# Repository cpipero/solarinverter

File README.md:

# solarinverter
Kicad Project to build a programmable Solar Inverter

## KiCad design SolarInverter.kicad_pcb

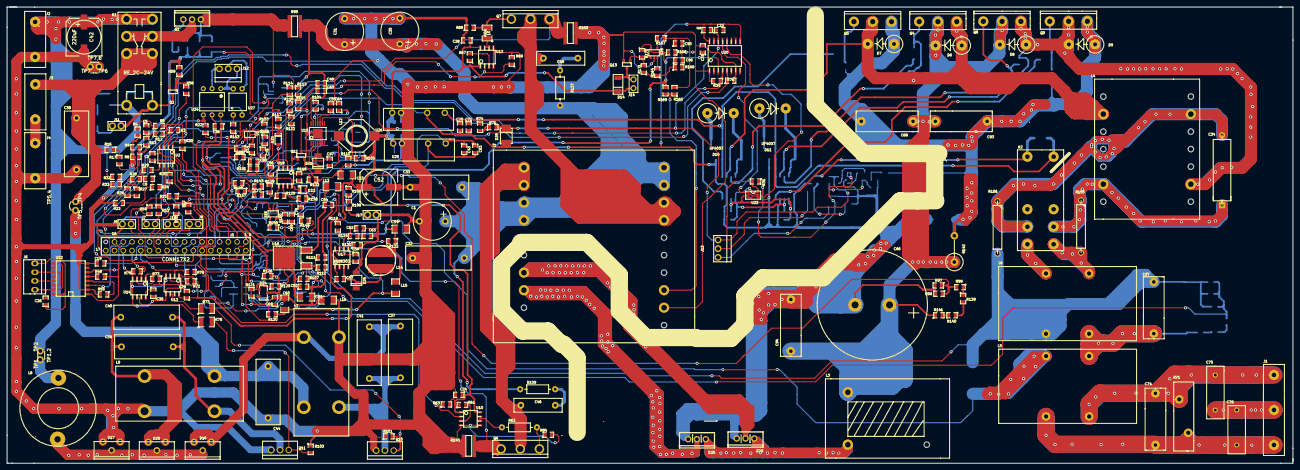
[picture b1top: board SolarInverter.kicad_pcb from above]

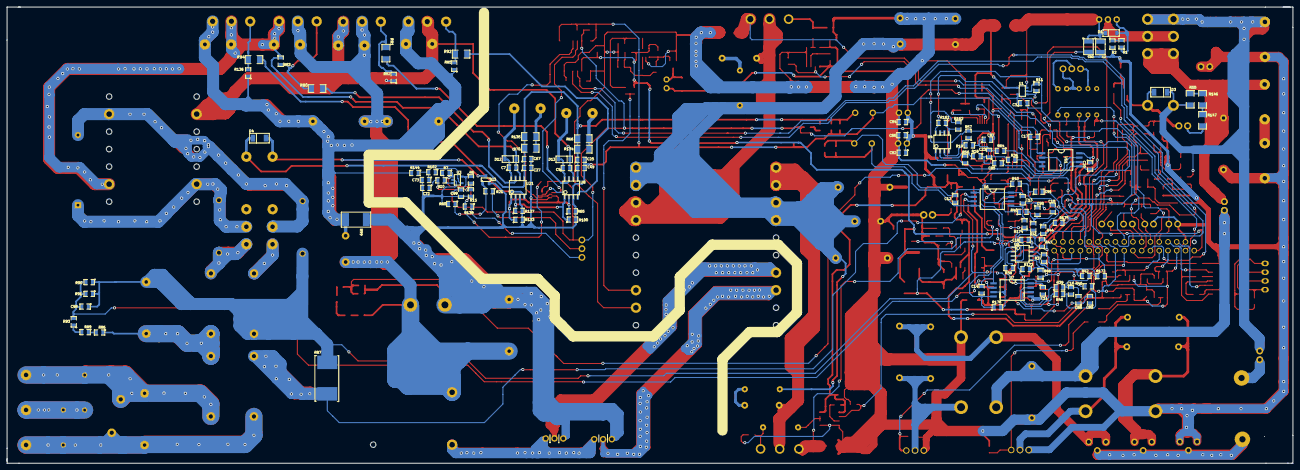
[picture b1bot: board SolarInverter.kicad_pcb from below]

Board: 2 copper layers, 373.0 x 132.3 mm, 370 parts (110 on the bottom side), 207 nets.

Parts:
C1, C31, C35: 2200uF; Elco18x37
C2, C92: 3.3uF; SM1210
C3, C6, C56, C65, C85, C87, C88, C89, C90, C91: 0.22uF; SM0805
C5, C8, C16, C23: 1nF; SM0805
C7, C9, C10, C64: 0.47uF; SM0805
C11, C12, C13, C14, C17, C20, C21, C22, C24, C25, C27, C28, C29, C30, C43, C48, C49, C54, C61, C67, C70, C71, C82, C83, C84, C86: 2.2uF; SM0805
C15: 2.2nF; SM0805
C18, C36, C72, C77, C80, C95, C96: 0.1uF; SM0805
C19, C26, C50, C69, C81, C99: 1uF; SM0805
C32, C33, C37, C38, C39, C40, C41, C44: 4.7uF; MetFilCap1807
C34: 1uF; CP8
C42: 220uF; SMDSVP10
C45, C46: 4700uF; MetFilCap13x4
C47, C57: 0.022uF; SM0805
C51, C53: 10uF; SM1206
C52: 470uF; SMDSVP10
C55: 4700pF; SM0805
C58: 10uF; SM0805
C59, C60: 22uF; SM1206
C62, C63, C73: 1000pF; SM0805
C66: 330uF; SnapCap30x40
C68, C74, C93, C94, C97: 0.15uF; MetFilCap2008
C75, C76: 2200pF; CP4
C78, C79: 47pF; SM0805
C98: 0.01uF; SM0805
D1: MMSZ5245B; SOD123
D3, D4, D14: RLS4148; SOD80
D6, D7, D8, D9, D10, D11: UF4007
D12, D13: MMSZ5245B-15V; SOD123
D16, D17, D20: MBR1560
D21, D25: STPS340; STPS340U
D22: BZM55C27
D23: MMSZ8V2T1G
D24: LM4041
D26, D29: PF60SA60DS
D28: 1SMB5918B
J1: CTB9550/3AO; Conn10mmX3
J2, J3, J4: BAT; Conn10mm
J5: CONN17X2; PinArray17x2
J6: HDR1X4WL; Molex22232041
J7, J8, J9, J10, J11, J17: JUMPERSEL; 2PinHeaer
J12, J13: CONN3PIN; Molex2031
J14: HDR1X2; HDR1x2
K1: RE_2C-24V; RE_2C_24V
K2: HRM1-S-12V; DPDTRelay
L3: 150uH; DMT21493L8
L4: 2X3.3mH; CoilL4
L5, L6: 2X6.8mH; PowerInductor1
L7, L9: 2X300uH; CMT1-.3-15L
L8: 47uH; PCV047310L
L12: 150uH; DO3316P-154KL
L13, L15, L16: 600OHM; SM1206
L14: 10uH; CDRH6D38NP
Q1: FQP47P06; FQP47P06TO220
Q2, Q3, Q12, Q13: BSS138LT1G; SOT23
Q4, Q5, Q8, Q9: FQA19N60; TO3PN
Q6, Q7: FDH3632
Q10, Q11: FDP3651U
R1, R2, R61, R67, R72, R77, R118, R124, R148, R152, R166: 22k; SM0805
R3, R5, R12, R20, R21, R24, R29, R53, R54, R59, R60, R117, R119, R132, R164, R165, R167, R168: 10k; SM0805
R4, R13, R23, R28, R51, R52, R163: 220; SM0805
R6: 20k; SM0805
R7: 1.5M; SM0805
R8, R26: 82k; SM0805
R9, R14, R15, R27, R120, R143, R149, R151, R153, R157, R158, R159: 1k; SM0805
R10, R84, R88, R101, R102, R103: 2.2k; SM0805
R11, R56, R57, R172, R173, R174, R175: 46.4k; SM0805
R16, R32: 27k; SM0805
R17, R33: 820; SM0805
R18, R19, R37, R38, R41, R42, R44, R46, R47, R48: 23.2k; SM0805
R22, R31, R34, R63, R65, R69, R75, R76, R79, R100, R127, R133, R150, R170: 4.7k; SM0805
R25, R30: 6.81k; SM0805
R36, R39, R40, R43, R45, R64: 3.32k; SM0805
R49, R58: 3.3k; SM0805
R50, R106, R108: 470; SM0805
R55, R146, R147: 1.5k; SM1206
R62, R109, R137: 10; CF14CT52R100J
R66, R70, R134, R135: 5.6; SM1206
R68, R73, R78: 10; SM1210
R71, R74, R138: 390; SM0805
R80, R81, R92, R94: 10; SM1206
R82, R83, R85, R96, R111, R112, R129, R136: 1.5k; SM0805
R86, R89, R93, R98, R139, R140, R141: 750k; SM0805
R87: 0.1; MetalStripR
R90, R144: 1.2k; SM0805
R91, R97: 1M; SM0805
R95, R145, R160: R005; FCSL64R005FER
R99: 0.05; RES2512
R104, R113, R115, R116, R126, R128, R130, R161, R162: 47k; SM0805
R105: 6.8k; SM0805
R107: 240; SM0805
R110, R125: 1.8k; SM0805
R114: 3.3.k; SM0805
R121: 5.1k; SM0805
R122, R171: 10M; SM0805
R123: 120k; SM0805
R131: 2.21k; SM0805
R142: 1.8M; R1WVERT
R155, R156: 330; R6
R169: 43k; SM0805
R176: 0; SM0805
RV1: 20S0271; VARISTOR
T1: ETD49
TP1,2: TP1___TP2; TP2PIN
TP5,4: TP5___TP4; TP2PIN
TP7,6: TP7___TP6; TP2PIN
U1: INA169
U2, U4, U9: AD8552; so-8
U3, U5, U19, U28: LMV7235M5; INA169
U6, U7, U11: ACPL-C78A; ACPL-C78A-060E
U8, U21: FAN7390; so-8
U10, U12, U13, U14: FAN3122; so-8
U15: LM5010A
U16: LM317MDT; DPAK2
U17: FAN8303; so-8
U18: LM393; so-8
U20: ADUM2200
U22: ADM2484E; SOIC16-W
U23: NL27WZ08
U24: PC900V0NSZXF
U25: MEV1S1205SC
U26: NMK1215SAC; MEV1S1205SC
U27: PS2561

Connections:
+1.65V_REF: C61.1, D24.2, R25.1, R30.1, R47.2, R48.1, R120.2, R121.1
+3.3V: C19.1, C21.1, C59.1, C69.1, C81.1, J5.A7, J5.B6, L14.2, L15.1, R22.1, R49.1, R51.1, R52.1, R53.1, R54.1, R132.1, R148.2, R150.1, R152.2, R163.1, R166.1, R169.1, R170.1, U5.5, U19.5, U20.3, U22.1, U28.5
+3.3VA: C3.1, C6.1, C18.1, C60.1, J5.A1, L15.2, R120.1, R161.2, U1.5, U2.8, U4.8, U9.8
+5VA: C11.1, C13.1, C20.1, C36.1, C50.1, C51.1, R107.1, U6.8, U7.8, U11.8, U16.2, U24.6
+12V: C24.1, C28.1, C29.1, C30.1, C52.1, C53.1, C82.1, C84.1, C86.1, D14.2, J14.1, L12.2, L13.1, R61.1, R67.1, R72.1, R77.1, R105.1, R106.1, R119.1, U10.1, U10.8, U12.1, U12.8, U13.1, U13.8, U14.1, U14.8, U17.2, U25.1, U26.1
/AnalogSensing/+36V: C1.1, C31.1, C32.2, C33.2, C35.1, C48.1, C65.1, R95.1, R104.1, R109.2, R137.1, T1.3, T1.4, T1.19, T1.20, U1.4, U15.13
/AnalogSensing/DCB_BAT: C42.1, D3.2, J2.1, K1.1, K1.4, K1.5, R32.2, R55.1, TP1,2.1
/AnalogSensing/DCB_SOLAR: C38.1, J3.1, K1.2, K1.7, R16.2, TP5,4.2
/AnalogSensing/DCB_pos: C2.1, C92.1, D1.1, Q1.S, R95.2, R113.1, R114.1, U1.3
/AnalogSensing/DC_0: C10.1, C17.2, C22.2, C25.2, C27.2, C49.2, C66.2, C67.2, C70.2, C71.2, C72.2, C73.2, C94.2, C99.2, D26.3, D28.2, D29.3, Q3.2, R15.2, R60.2, R65.2, R96.2, R97.2, R99.1, R100.2, R127.2, R133.2, U3.2, U8.3, U11.3, U11.4, U20.9, U20.16, U21.3, U23.4, U26.3
/AnalogSensing/DC_5: C10.2, C17.1, C22.1, C99.1, D28.1, J13.1, R6.1, R31.2, R71.2, U3.5, U11.1, U20.14, U23.8
/AnalogSensing/GND_S: C12.2, C14.2, C43.2, C83.2, R176.1, U6.4, U7.4, U25.3
/AnalogSensing/I_sense_P: J5.B2, R11.2, U1.1
/AnalogSensing/I_sense_S: J5.A3, R38.2, U9.1
/AnalogSensing/I_sense_S1: L5.1, R87.2, U6.2
/AnalogSensing/I_sense_S2: C97.2, C98.1, L6.4, R87.1, R90.1, R91.1, R156.2, R176.2, U6.3, U7.3
/AnalogSensing/U_sense_BAT: J5.B4, R20.2, U2.7
/AnalogSensing/U_sense_DC2: R96.1, R97.1, R98.2, U11.2
/AnalogSensing/U_sense_DCB: J5.A5, R56.2, U4.1
/AnalogSensing/U_sense_P: J5.B3, R3.2, U2.1
/AnalogSensing/U_sense_PL1: C98.2, R90.2, R91.2, R93.2, U7.2
/AnalogSensing/U_sense_S: J5.A4, R37.2, U9.7
/AnalogSensing/V_DC_S_pos: C12.1, C14.1, C43.1, C83.1, U6.1, U7.1, U25.4
/Control/DC_5_C: J12.1, U24.1, U27.4
/Control/FAULT_LED: J5.B10, J8.2
/Control/FBFault: J5.A16, R22.2, U24.4
/Control/K_DC: D3.1, J11.1, K1.8, Q2.3
/Control/OFFGRID_SW: J5.B13, J9.1, R54.2
/Control/OFF_GRID_LED: J5.B11, J10.2
/Control/Opto_C: J12.3, U24.2
/Control/PWM_CHA: J5.A13, R75.1, U13.2
/Control/PWM_CHB: J5.A14, R79.1, U14.2
/Control/PWM_PA: J5.A9, R63.1, U10.2
/Control/PWM_PB: J5.A10, R69.1, U12.2
/Control/PWM_SA: J5.A11, R34.1, U20.4
/Control/PWM_SB: J5.A12, R76.1, U20.5
/Control/Power_SW: J12.2, U27.3
/Control/RELAY: J5.B8, R58.1
/Control/RELAY_P: J5.B9, U27.2
/Control/RS485-A: J6.2, U22.11, U22.14
/Control/RS485-B: J6.3, U22.12, U22.13
/Control/RS485-GND: C26.2, J6.4, U22.9, U22.15
/Control/RS485-VDD: C26.1, J6.1, U22.16
/Control/RxD: J5.B15, U22.3
/Control/START_SW: J5.B12, J7.1, R53.2
/Control/TxD: J5.B14, U22.6
/MOSFETDrivers/Bridge_A: C9.2, D6.1, D7.2, D13.1, L4.1, Q4.2, Q5.3, R82.1, U8.6
/MOSFETDrivers/Bridge_B: C7.2, D8.1, D9.2, D12.1, L4.3, Q8.2, Q9.3, R83.1, U21.6
/MOSFETDrivers/DC_18: C25.1, C27.1, C49.1, C67.1, C70.1, C71.1, D4.2, K2.8, R66.1, R70.1, R74.1, R134.1, R135.1, U8.5, U21.5, U26.4
/MOSFETDrivers/Fault_FB: R7.1, R31.1, R138.2, U3.1, U23.2, U23.6
/MOSFETDrivers/G_OUTA: R100.1, R127.1, U8.1, U21.2, U23.7
/MOSFETDrivers/G_OUTB: R65.1, R133.1, U8.2, U21.1, U23.3
/MOSFETDrivers/Gate_CHA: Q10.1, R73.2, R101.2
/MOSFETDrivers/Gate_CHB: Q11.1, R78.2, R103.2
/MOSFETDrivers/Gate_PA: Q6.1, R62.2, R84.1
/MOSFETDrivers/Gate_PB: Q7.1, R68.2, R88.2
/MOSFETDrivers/Gate_SA1: R81.1, U8.7
/MOSFETDrivers/Gate_SA2: R92.1, U8.4
/MOSFETDrivers/Gate_SB1: R80.1, U21.7
/MOSFETDrivers/Gate_SB2: R94.1, U21.4
/MOSFETDrivers/OUTA: U20.13, U23.1
/MOSFETDrivers/OUTB: U20.12, U23.5
/PowerCircuit/DC_400: C66.1, C68.1, C93.1, C94.1, D6.2, D8.2, L3.2, Q4.3, Q8.3, R141.1, R142.1
/PowerCircuit/FAN: D14.1, J14.2, Q13.3
/PowerCircuit/Falut_PP: J5.A17, R150.2, U5.1, U19.1
/PowerCircuit/I_DCB_Fault+: C68.2, C93.2, D7.1, D9.1, Q5.2, Q9.2, R85.1, R99.2, R136.1, R142.2, R144.2
/PowerCircuit/I_sense_PA1: Q6.2, R145.1, R149.1
/PowerCircuit/I_sense_PB1: Q7.2, R153.1, R160.2
/PowerCircuit/Opto_C_R: J13.3, R138.1
/PowerCircuit/Power_Line_1: C74.1, C75.1, J1.3, L5.3, RV1.1
/PowerCircuit/Power_Line_2: C74.2, C76.2, J1.1, L5.4, RV1.2
/PowerCircuit/Therm_1: R165.1, R169.2, T1.13
/PowerSupplies/+27V: C56.2, D22.2, R114.2, R117.1, R118.1, R128.1, U18.8
GND: C1.2, C2.2, C19.2, C21.2, C24.2, C28.2, C29.2, C30.2, C31.2, C32.1, C33.1, C35.2, C38.2, C42.2, C44.2, C48.2, C52.2, C53.2, C55.2, C56.1, C58.2, C59.2, C62.2, C63.2, C64.2, C65.2, C69.2, C77.2, C78.2, C79.2, C80.2, C81.2, C82.2, C84.2, C86.2, C92.2, C95.2, C96.2, D17.1, D17.3, D22.1, D23.1, D25.1, J2.2, J4.2, J5.A8, J5.A15, J5.B7, J5.B16, J7.2, J9.2, J17.2, L7.4, L9.3, L16.1, Q2.2, Q10.2, Q11.2, Q12.2, Q13.2, R2.2, R4.1, R8.2, R9.2, R23.1, R26.2, R27.2, R34.2, R50.2, R59.2, R63.2, R69.2, R75.2, R76.2, R79.2, R84.2, R88.1, R101.1, R103.1, R110.2, R115.2, R123.2, R130.2, R131.2, R143.2, R145.2, R151.2, R160.1, R168.2, T1.12, TP7,6.1, TP7,6.2, U5.2, U10.4, U10.5, U12.4, U12.5, U13.4, U13.5, U14.4, U14.5, U15.5, U15.6, U15.15, U17.4, U18.4, U19.2, U20.1, U20.7, U22.2, U22.8, U25.2, U26.2, U28.2
GNDA: C3.2, C6.2, C11.2, C13.2, C18.2, C20.2, C36.2, C50.2, C51.2, C54.2, C60.2, C61.2, C85.1, C87.2, C88.1, C89.2, C90.1, C91.2, D24.3, J5.A2, J5.A6, J5.B1, J5.B5, L16.2, R11.1, R57.2, R111.2, R112.2, R125.2, R126.2, R162.1, R172.2, R173.1, R174.2, R175.1, U1.2, U2.4, U4.4, U6.5, U7.5, U9.4, U11.5, U24.5
GNDPWR: C75.2, C76.1, J1.2
unnamed: J3.2, J4.1
unnamed: K1.3, K1.6, Q1.D
unnamed: R1.2, R2.1
unnamed: D1.2, Q1.G, R1.1
unnamed: C7.1, D11.2, D12.2, U21.8
unnamed: D10.1, R66.2, R134.2
unnamed: C9.1, D10.2, D13.2, U8.8
unnamed: D11.1, R70.2, R135.2
unnamed: R72.2, U13.3
unnamed: R62.1, U10.6, U10.7
unnamed: R77.2, U14.3
unnamed: R67.2, U12.3
unnamed: R61.2, U10.3
unnamed: R78.1, U14.6, U14.7
unnamed: R73.1, U13.6, U13.7
unnamed: R68.1, U12.6, U12.7
unnamed: R98.1, R139.1
unnamed: R139.2, R140.1
unnamed: R140.2, R141.2
unnamed: R159.2, U5.4
unnamed: R14.2, U5.3
unnamed: C79.1, R153.2, R159.1
unnamed: C80.1, R14.1, R151.1, R152.1
unnamed: C44.1, L7.2, L9.1, TP5,4.1
unnamed: C37.1, C41.1, L7.3, Q10.3
unnamed: C39.1, C40.1, L9.4, Q11.3
unnamed: Q9.1, R94.2, R136.2
unnamed: Q8.1, R80.2, R83.2
unnamed: Q4.1, R81.2, R82.2
unnamed: Q5.1, R85.2, R92.2
unnamed: R7.2, R10.1, U3.3
unnamed: C78.1, R149.2, R158.1
unnamed: R157.2, U19.3
unnamed: R158.2, U19.4
unnamed: C77.1, R143.1, R148.1, R157.1
unnamed: C72.1, R6.2, R10.2, R15.1
unnamed: C73.1, R102.2, R144.1
unnamed: R102.1, U3.4
unnamed: R167.2, U28.4
unnamed: R164.2, U28.3
unnamed: Q13.1, R170.2, R171.2, U28.1
unnamed: C96.1, R164.1, R166.2, R168.1, R171.1
unnamed: C95.1, R165.2, R167.1
unnamed: R71.1, R74.2
unnamed: C39.2, C40.2, D20.1, D20.3, L9.2
unnamed: C37.2, C41.2, D16.1, D16.3, L7.1
unnamed: C34.1, K2.6, L4.2, R155.1
unnamed: D4.1, K2.1, Q3.3
unnamed: Q3.1, R21.2, R60.1
unnamed: C34.2, K2.3, L4.4, R156.1
unnamed: L8.2, TP1,2.2
unnamed: D16.2, D17.2, D20.2, L8.1
unnamed: J13.2, R21.1
unnamed: R89.2, R93.1
unnamed: R86.2, R89.1
unnamed: C97.1, L5.2, L6.3, R86.1
unnamed: K2.4, L6.1
unnamed: K2.5, L6.2, R155.2
unnamed: C45.2, Q7.3, T1.17, T1.18
unnamed: C46.1, Q6.3, T1.1, T1.2
unnamed: C45.1, R137.2
unnamed: C46.2, R109.1
unnamed: D29.2, T1.7
unnamed: D26.1, D29.1, L3.1
unnamed: D26.2, T1.8
unnamed: U4.6, U4.7
unnamed: R161.1, R162.2, U4.5
unnamed: C15.1, C90.2, R40.2, R41.1
unnamed: C15.2, C91.1, R43.2, R44.1
unnamed: R43.1, U6.7
unnamed: R44.2, R47.1, R175.2, U9.3
unnamed: R38.1, R41.2, R174.1, U9.2
unnamed: R40.1, U6.6
unnamed: R20.1, R24.2, R25.2, U2.6
unnamed: R29.2, U2.5
unnamed: C8.1, R23.2, R24.1
unnamed: C8.2, R28.2, R29.1
unnamed: R32.1, R33.1
unnamed: R26.1, R27.1, R28.1, R33.2
unnamed: C5.1, R4.2, R5.1
unnamed: R3.1, R5.2, R30.2, U2.2
unnamed: R12.2, U2.3
unnamed: C5.2, R12.1, R13.2
unnamed: R8.1, R9.1, R13.1, R17.2
unnamed: R16.1, R17.1
unnamed: R46.2, R48.2, R173.2, U9.5
unnamed: R19.2, R57.1, U4.3
unnamed: R18.2, R56.1, U4.2
unnamed: R37.1, R42.2, R172.1, U9.6
unnamed: R36.1, U11.6
unnamed: R64.1, U11.7
unnamed: R39.1, U7.6
unnamed: R45.1, U7.7
unnamed: C16.2, C89.1, R45.2, R46.1
unnamed: C16.1, C88.2, R39.2, R42.1
unnamed: C23.1, C85.2, R18.1, R36.2
unnamed: C23.2, C87.1, R19.1, R64.2
unnamed: R113.2, R115.1, R116.1
unnamed: R116.2, R122.1, U18.2
unnamed: D23.2, R117.2, U18.3
unnamed: R119.2, U17.7
unnamed: Q12.1, R118.2, R122.2, R123.1, U18.1
unnamed: C64.1, U15.12
unnamed: C54.1, L13.2, U16.3
unnamed: R128.2, R129.1, U18.5
unnamed: R129.2, R130.1, U18.6
unnamed: D24.1, R121.2, R125.1, R126.1
unnamed: C62.1, R124.1, U17.6
unnamed: C63.1, R124.2
unnamed: C58.1, U17.8
unnamed: R131.1, R132.2, U17.5
unnamed: C57.1, U17.1
unnamed: C57.2, D25.2, L14.1, U17.3
unnamed: J17.1, R108.2
unnamed: R106.2, R108.1
unnamed: C47.1, U15.3
unnamed: R107.2, R111.1, R112.1, U16.1
unnamed: C55.1, U15.10
unnamed: D21.1, U15.4
unnamed: R105.2, R110.1, U15.9
unnamed: C47.2, D21.2, L12.1, U15.2
unnamed: Q12.3, R104.2, U15.11
unnamed: J11.2, R147.2
unnamed: Q2.1, R58.2, R59.1
unnamed: R146.2, R147.1
unnamed: R55.2, R146.1
unnamed: R50.1, U22.4
unnamed: R49.2, U22.5
unnamed: J10.1, R51.2
unnamed: J8.1, R52.2
unnamed: R163.2, U27.1

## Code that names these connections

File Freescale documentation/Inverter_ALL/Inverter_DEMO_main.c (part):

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#define PWM_BAT		MC_PWM_SIGNAL_4 | MC_PWM_SIGNAL_5

//------GPIO_B definitions for 8023 inverter board-------
#define START_SW	BIT_0
#define OFFGR_SW	BIT_1
#define FAULT_LED	BIT_2
#define OFF_G_LED	BIT_3
#define RELAY		BIT_4
#define RELAY_P		BIT_5

//-------------------------------------------------------------------------------------------------
/* Variables */
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	
	archEnableInt();
	
	ioctl(GPIO_B, GPIO_SET_PIN, FAULT_LED);	// deactivate FAULT_LED;
	ioctl(GPIO_B, GPIO_SET_PIN, RELAY_P);	// deactivate RELAY_P;
	f16DCBVoltSet = DCBVOLT_FRAC16;			// desired value of the DCBus Voltage;
//-------------------------------------------------------------------------------------------------	
	while(1)
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			//---------------OFF_GRID mode-------------------------------------
			u8OutGenState = OFF_GRID;
			u8OutGenState = OFF_GRID;
			ioctl(GPIO_B,GPIO_CLEAR_PIN,RELAY_P);		// switch ON the power relay;
			ioctl(GPIO_B, GPIO_CLEAR_PIN, OFF_G_LED);	// activate OFF_G_LED;
			//-----------------------------------------------------------------
    		
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 		
//-----------------Check Control Switches----------------------------------------------------------
		CntrlSwitchTest();		// check the switches ON/OFF and OFF_GRID;
		if(u16Fault) ioctl(GPIO_B, GPIO_CLEAR_PIN, FAULT_LED);			// activate FAULT_LED;
		else if(!u16Fault) ioctl(GPIO_B, GPIO_SET_PIN, FAULT_LED);		// deactivate FAULT_LED;

//-----------------Check DCBus Voltage level-------------------------------------------------------
		if(f16DCBAvg > DCBLLIM_FRAC16) u8PWM_S_state = UP;
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				u8sine_crossH = 0;
				f16PWMOutput = FRAC16(0.5);					// PWM_S input;
				ioctl(PWM, PWM_OUTPUT_PAD, PWM_DISABLE);	// switch OFF PWMs;
				ioctl(GPIO_B, GPIO_SET_PIN, RELAY_P);		// switch OFF the power relay;
				u8StartSwitch = STOP;
				u8PWM_P_state = DOWN;
				u8PWM_S_state = DOWN;
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	{
		Init_Variables();

		if((ioctl(GPIO_B, GPIO_READ_DATA, NULL) & START_SW) == 0)
		{
			u8StartSwitch = RAMP;
			u16LoopSwitch1Cnt = 200;
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	{
		if(!u16LoopSwitch1Cnt) 
		{
			if((ioctl(GPIO_B, GPIO_READ_DATA, NULL) & START_SW) == 0)
			{
				f16DCBVoltSet = DCBVOLT_FRAC16;		// desired value of the DCBus Voltage;
				u8StartSwitch = RUN;
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//-----------------------------------------------------------------------------
	if(u8StartSwitch == RUN)
	{
		if((ioctl(GPIO_B, GPIO_READ_DATA, NULL) & START_SW) == START_SW)	// START_SW switched OFF;
		{
			u8StartSwitch = GO_DOWN;				// Controlled SWITCH_OFF process;
		}
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
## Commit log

2015-03-17 first push
2015-03-17 Create gh-pages branch via GitHub
2015-11-11 added original documentation
